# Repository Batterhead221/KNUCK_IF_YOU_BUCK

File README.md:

KNUCK_IF_YOU_BUCK

Custom LMR51430 buck converter PCB (12V → 5V @ ~0.5A, designed with ~1A headroom).

TEST BOARD - NO FAB

Key features
	•	Optimized SW node geometry
	•	Tight input loop placement (VIN decoupling kept close)
	•	Clean feedback routing with isolation from noisy nodes
	•	Short switching loops for better EMI behavior
	•	Clear grounding strategy (return paths kept compact)
	•	Debug-friendly access (VIN, SW, FB, EN, 5V)

Hardware design
	•	Converter: TI LMR51430
	•	Input: 12V
	•	Output: 5V (target 0.5A, with ~1A headroom)
	•	Inductor: 6.8µH power inductor (500 kHz design choice)
	•	Feedback divider: 100k / 13.7k (sets 5V output)
	•	Output caps: 2×22µF + local decoupling
	•	Input caps: 22µF + 0.1µF placed close to VIN/GND 

Layout priorities
	•	Tight high-current loop: VIN → SW → L → COUT → GND
	•	Keep SW copper small (short + compact)
	•	Solid ground reference near power stage
    
Designed and engineered by Brandon Shelly

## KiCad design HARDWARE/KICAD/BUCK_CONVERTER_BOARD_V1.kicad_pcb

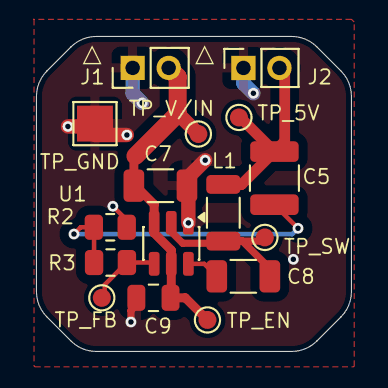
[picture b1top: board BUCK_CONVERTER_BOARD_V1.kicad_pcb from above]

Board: 2 copper layers, 17.5 x 17.5 mm, 16 parts (0 on the bottom side), 7 nets.

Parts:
C5: 47UF; C_1210_3225Metric
C7: 10UF; C_1206_3216Metric
C8: 0.1UF; C_1206_3216Metric
C9: 0.1UF; C_0805_2012Metric
J1: V/IN_CONN; PinHeader_1x02_P2.00mm_Vertical
J2: V/OUT_CONN; PinSocket_1x02_P2.00mm_Vertical
L1: 10UH; L_1206_3216Metric
R2: 20K; R_0805_2012Metric
R3: 100K; R_0805_2012Metric
TP_5V: TP_5V; TestPoint_Pad_D1.0mm
TP_EN: TP_EN; TestPoint_Pad_D1.0mm
TP_FB: TP_FB; TestPoint_Pad_D1.0mm
TP_GND: TP_GND; TestPoint_Pad_2.0x2.0mm
TP_SW: TP_SW; TestPoint_Pad_D1.0mm
TP_V/IN: TP_VIN; TestPoint_Pad_D1.0mm
U1: LMR51430; SOT-23-6

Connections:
/+5V_BUCK: C5.2, J2.2 (PWR), L1.2, TP_5V.1
/FB: R3.2, TP_FB.1, U1.4 (FB)
/SW: C8.2, L1.1, TP_SW.1, U1.2 (SW)
/V/IN: C7.2, C9.1, J1.2 (V/IN), TP_EN.1, TP_V/IN.1, U1.3 (VIN), U1.5 (EN)
GND: C7.1, C9.2, J1.1 (GND), J2.1 (GND), R2.1, TP_GND.1, U1.1 (GND)
unnamed: C5.1, R2.2, R3.1
unnamed: C8.1, U1.6 (CB)

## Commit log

2026-02-13 Buck Converter
    Custom 12V → 5V buck converter
2026-02-17 EDIT
    CHANGED CURRENT RATING AND ADDED DIODE TO SCHEMATICS
2026-03-03 V2
    V2
2026-03-03 UPDATE
    UPDATE
